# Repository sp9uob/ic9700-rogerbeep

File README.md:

RogerBeep dongle for Icom IC-9700 designed to fit in accessory plug

73! Tom SP9UOB

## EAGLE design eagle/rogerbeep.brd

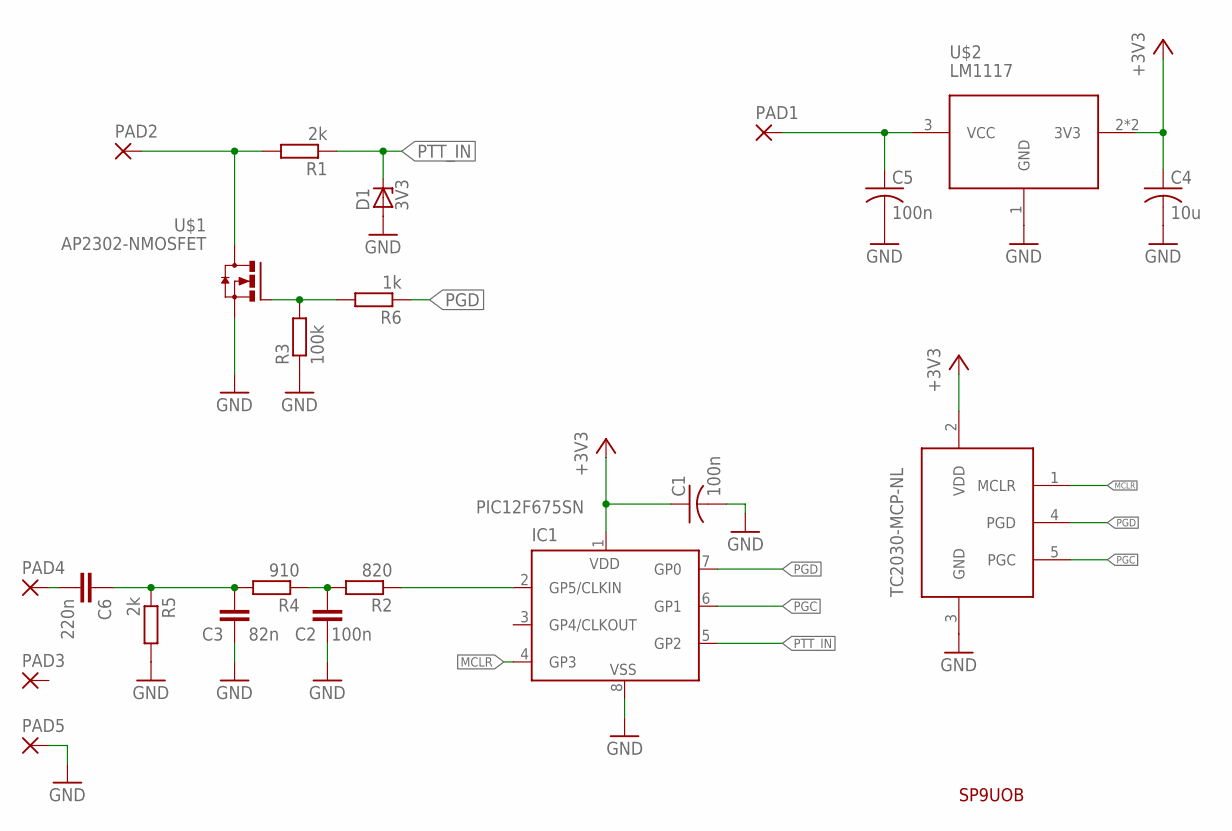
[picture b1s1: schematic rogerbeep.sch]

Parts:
C1, C5: 100n; C0805
C2: 100n; C0603
C3: 82n; C0603
C4: 10u; C0805
C6: 220n; C0603
D1: 3V3; SOT23
IC1: PIC12F675SN; SO-08
PAD1, PAD2, PAD3: SMD5; SMD2,54-5,08
PAD4, PAD5: SMD2; SMD1,27-2,54
R1, R5: 2k; R0603
R2: 820; R0603
R3: 100k; R0603
R4: 910; R0603
R6: 1k; R0603
U$1: AP2302-NMOSFET; SOT23-3
U$2: LM1117; SOT223-3
U$5: TC2030-MCP; TC2030-IDC-NL

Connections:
13.8V: C5.1, PAD1.1, U$2.3 (VCC)
+3V3: C1.1, C4.1, IC1.1 (VDD), U$2.2 (3V3), U$2.4 (3V3), U$5.2 (VDD)
GND: C1.2, C2.1, C3.1, C4.2, C5.2, D1.1 (A), IC1.8 (VSS), PAD5.1, R3.1, R5.2, U$1.2 (S1), U$2.1 (GND), U$5.3 (GND)
MCLR: IC1.4 (GP3), U$5.1 (MCLR)
MOD: C3.2, C6.1, R4.2, R5.1
unnamed: IC1.2 (GP5/CLKIN), R2.1
unnamed: PAD2.1, R1.2, U$1.3 (D1)
unnamed: C2.2, R2.2, R4.1
unnamed: C6.2, PAD4.1
unnamed: R3.2, R6.2, U$1.1 (G1)
PGC: IC1.6 (GP1), U$5.5 (PGC)
PGD: IC1.7 (GP0), R6.1, U$5.4 (PGD)
PTT_IN: D1.3 (C), IC1.5 (GP2), R1.1

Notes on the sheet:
SP9UOB

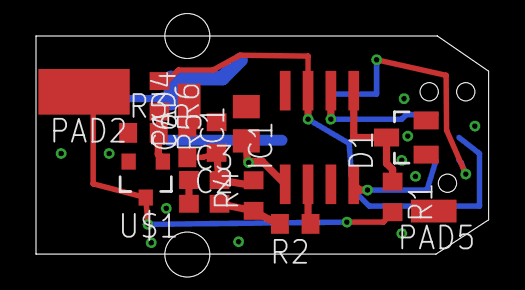
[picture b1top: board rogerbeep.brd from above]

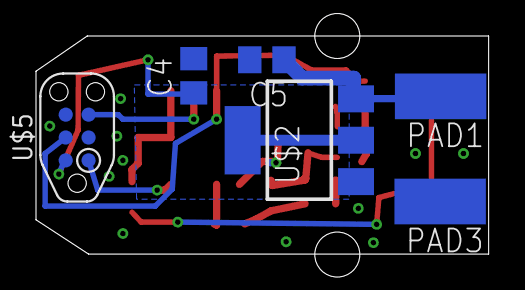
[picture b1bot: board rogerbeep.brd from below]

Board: 2 copper layers, 25.1 x 12.1 mm, 22 parts (6 on the bottom side), 13 nets.

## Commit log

2021-03-23 cleanup
